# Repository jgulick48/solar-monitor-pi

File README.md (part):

# solar-monitor-pi

A Raspberry Pi image for monitoring a solar installation that uses EG4 / LuxPower inverters with the
WiFi datalogger dongle. Plug the Pi into the same network as the dongles and it finds them, starts
collecting data and serves dashboards. Nothing is sent to the internet, and the inverters are only
read, never changed.

## What's on it

| Part | What it does | Where |
|---|---|---|
| Setup page | Start page: dongles found, links, site setup form | `http://<pi>/` (port 80) |
| [lxp-bridge-go](https://github.com/jgulick48/lxp-bridge-go) | Reads every inverter's dongle (read-only mode) and publishes the values | internal |
| Mosquitto | MQTT broker between the bridge and Home Assistant | localhost only |
| VictoriaMetrics | Long-term history (5 years) of every inverter value | localhost only |
| Grafana | Dashboards, viewable without logging in | `http://<pi>:3000` |
| Home Assistant | Inverter entities (MQTT discovery), the Solar dashboard, alerts to phones | `http://<pi>:8123` |
| Advisor | Weekly analysis: batteries, panels, inverter or generator? | `http://<pi>/advisor` |
| Backups | Nightly backup to a USB stick, and restore | `http://<pi>/backup` |
| Battery health | Cell spread near full, temperatures, SOH, cycles, capacity check, BMS faults | `http://<pi>/battery` |
| Panels and inverters | A PV string or an inverter making far less than usual; the site far below the sunlight | `http://<pi>/panels` |
| Monthly report | Last month's solar, use, generator, battery and backups, against a year earlier | `http://<pi>/report` |
| Generator log | Every generator run, hours since the last service, service reminder | `http://<pi>/generator` |
| Wall display | Dashboard and up to two cameras on a screen plugged into the Pi's HDMI port | `http://<pi>/display` |
| go2rtc | Turns the cameras' RTSP(S) streams into video the display's browser can play | localhost only |
| cloudflared | Optional remote access to Home Assistant through your own Cloudflare account | `https://<name>.<your domain>` |
| cloudflared-support | Optional remote support: a helper's own Cloudflare Tunnel, while the owner allows it | the helper's hostnames |

## Hardware

- Raspberry Pi 4 (2 GB is enough, 4 GB recommended) and the official 5.1 V 3 A power supply.
- A **128 GB SSD** in a USB 3 enclosure with UASP (or a USB SSD such as a Samsung T7 / SanDisk Extreme).
  Five years of history for two inverters is a few GB; the extra space spreads the writes so the drive
  lasts. SATA-in-USB enclosures are safer than NVMe on a Pi 4 (its USB ports share about 1.2 A).
- Wired Ethernet on the same network (subnet) as the inverter dongles.
- Optional: a 1080p monitor or TV on the Pi's HDMI port (micro-HDMI 0, next to the power socket) for the
  wall display. Plugging it in, even later, starts the display.

## First boot

1. Flash the image to the SSD, plug it into the Pi's blue USB 3 port, connect Ethernet, power on.
2. Wait about five minutes, then open `http://solar-monitor.local/` (or the Pi's IP from the router).
3. The start page lists the dongles it found. Click **Finish setup** and enter the location, time zone,
   batteries, panels and generator. Saving applies it to Home Assistant and Grafana. The setup page lists its
   sections down the left side (a row of buttons under the header on a phone): the ones saved together with
   **Save site settings** have a green edge, the ones with their own button a blue edge. The list follows the
   page as it scrolls and marks sections with unsaved changes.
4. Open Home Assistant from the start page and create your account. The inverter entities are already
   there.

Give each dongle a fixed IP (DHCP reservation) in the router if you can. If a dongle's IP changes anyway,
the hourly scan finds it again by its serial number.

## Wall display

With a screen on the HDMI port the Pi shows a dashboard, laid out for 1920x1080:

- **Cameras** (left half, two stacked 960x540 tiles; without cameras the power figures use the whole screen).
- **Battery** (%, kWh stored, how long it lasts at the usual use), **solar**, **house load**, **battery power**
  (charging/discharging) and **generator**, with today's totals and the last 24 hours as a chart.
- **Notes**: dongles offline, inverter faults, low battery and, for a hand-started generator, from mid-afternoon on
  whether the battery lasts until the sun is back ("Start the generator before dark: ... about 4.2 kWh more is
  needed"), from the house's expected use and the solar forecast: a dull day tomorrow counts too
  ("tomorrow looks dull (about 6 kWh of solar expected) ...").
- **Any screen**: the screen mode comes from the TV's EDID: its own preferred mode, except that screens bigger than
  1920x1200 (4K TVs) run at 1920x1080, which the Pi handles much better with cameras and the TV scales up. The layout
  scales with the tighter of width and height, so 4:3, 16:10, 21:9 and 720p/768p screens fit, and a screen on its
  side gets the cameras on top and the figures below. The setup page shows the screen found and the mode used.
- **Clock**: 12-hour (4:41 PM) or 24-hour, set on the setup page (by default 12-hour with US units); the same format is
  used in the generator advice and the daily summary.
- **Sounds**: short chimes through the screen's speakers (HDMI) when a UniFi Protect camera sees something (a car horn for vehicles): doorbell
  ring and person by default, vehicle, animal and package optional, with a volume and *not during the screen-off
  hours*. *Play a test sound* on the setup page checks it. Repeats are limited: the same alert (same camera, same
  kind) at most once a minute by default, any two sounds at least 5 seconds apart, and the doorbell always rings
  (all adjustable); the camera still comes to the front of the screen. The kiosk points its sound at the HDMI port the screen is
  on (`~solar-display/.asoundrc`, Pi 4: HDMI-A-1 = vc4hdmi0); the screen or TV needs speakers.
- **Voice announcements** (optional, like UniFi's Alarm Manager; setup page: *Optional features* → *Voice
  announcements*): after the chime, or instead of it, Piper says what a camera saw, "Person at the Front door" /
  "Someone's at the Front door" (wording under *Cameras*, `{object}` and `{camera}`), in one of four English
  voices. Other features can use it for their own alerts (`modules.voice.announce(stack, text, chime=...)`; the display
  speaks announcements from the last two minutes, not during quiet hours). Piper runs in the optional `tts` service
  (`rhasspy/wyoming-piper`, the voice Home Assistant uses for local voice); it isn't in the image (about 200 MB):
  turning voice on downloads it and the voice once, then it works offline. Phrases are made ahead of time and cached
  (`state/tts-cache`). *Play a test announcement* on the setup page checks it.
- **Burn-in protection**: every 20 minutes the layout changes (cameras on the left or the right, or without cameras
  the tiles in order or reversed; the figures top-down or flipped, clock at the bottom), with a short fade, and every
  minute the whole page drifts a few pixels along a small circle, so no label, border or grid line stays on the same
  pixels for hours. `http://<pi>/display?layout=0` (to 3) shows one layout without rotating. The screen can also be
  switched off for set hours on the setup page.

### Solar forecast

`solar-collector` keeps Open-Meteo's irradiance forecast for each array (the same hourly request it already makes)
and turns it into expected output per hour for today and the next five days (`state/forecast.json`), scaled by the
advisor's calibration of this site's panels once it has one (0.8 of the model until then) and capped at the
inverters' solar input. It shows on the display's solar tile, as `sensor.site_solar_forecast_today` / `_tomorrow` in
Home Assistant, and drives the generator advice, which steps the battery through tonight and tomorrow in 15-minute
steps (forecast solar against the usual use) instead of assuming the sun takes over two hours after sunrise. With no
fresh forecast (no internet) the advice falls back to that rule.

It runs Chromium in kiosk mode inside `cage` (a one-app Wayland compositor; no desktop) as the locked
`solar-display` account (`solar-display.service`). It only starts when the display is turned on on the setup page,
the kiosk software is installed and a screen is connected; plugging a screen in starts it (udev rule). The browser's
profile lives in RAM. The same page is at `http://<pi>/display` from other computers, without the cameras.

**Camera checks.** The box re-fetches UniFi Protect's stream links at startup and every hour when Protect has changed
them (an old link can connect and send nothing), and checks each camera's video codec. The screen plays H.264 only: a
camera sending H.265 (Protect's *Enhanced Encoding*) shows a note in its place instead of a black box, and the setup
page says so; turn Enhanced Encoding off for that camera in Protect.

**Dongles that are gone** (a replaced dongle, a box moved to another site, test simulators) can be removed with
*Forget* on the start page: from the monitor, the bridge and Home Assistant.

**Camera load.** Playing the camera video is nearly all of the box's CPU work (test Pi 4: 41% of its four
cores with two medium-quality UniFi Protect streams, 27% with low, 5% with no video). The Protect section's *Camera
picture* is *Automatic* by default: low on a Pi 4, medium on a Pi 5 (boxes that update switch by themselves). The
video stops while the screen is off. go2rtc runs on the host network, listening on 127.0.0.1 only.

**Weather** shows in the same panel as the solar figures (setup page: *Optional features* → *Weather*, on by default;
how many forecast days and how fast they page are under *Weather on the screen*): now (temperature, conditions, feels-like, wind speed, gusts and direction, humidity, rain today), the next
days (high/low, rain chance, wind) and, where there's room, the next 12 hours. The forecast comes from Open-Meteo (free,
no key; every 30 minutes); a weather station set up on the setup page (Ecowitt, Tempest, WeatherLink, or pushing to
the box) supplies "now" with its own readings, wind included. In the US, National Weather Service alerts for the site
(every 10 minutes) appear with the other notes, red for severe ones. If the panel doesn't fit the screen (long notes, a
small screen), the hourly row is left out first.

**When the screen is on** (setup page, *Screen*): always; during **on-hours** (up to four lines such as
Mon-Fri 06:30-22:00 and Sat-Sun 08:00-01:00, past midnight allowed); **when someone's in the room**, from Home
Assistant occupancy, motion or presence sensors (`binary_sensor.*`, `person.*`, `input_boolean.*`; stays on for a set
time after the room empties); or during the on-hours *and* when someone's there. Camera events (doorbell, person, ...)
can turn it on for a few minutes outside those times. When it's off, the HDMI picture is switched off (`wlr-randr`;
most monitors and many TVs go to standby by themselves) and, if ticked, the **TV is put in standby and woken over
HDMI-CEC** (`cec-ctl`; SimpLink, Anynet+, Bravia Sync...), switched to the box's input when it wakes. The setup page
shows whether the TV answers CEC, and *Test: screen off for 15 seconds* tries it. Occupancy reaches the box through an
automation the box writes into Home Assistant (`packages/solar_display.yaml`); if Home Assistant goes quiet for 20
minutes the screen stays on. `solar-display-power.service` does the switching; CEC is sent only when the screen's state
changes, so a TV turned off with its remote stays off until the next change.

### Cameras (UniFi Protect)

Cameras are an optional feature (setup page: *Optional features* → *Cameras*; on for boxes that had cameras
before). Turning it off stops go2rtc and the Protect event listener and keeps the camera settings.

Up to 16 cameras; two are on screen at a time and they take turns every 15 seconds (only the two on screen are
played, so more cameras don't load the Pi).

**From UniFi Protect** (setup page, *UniFi Protect cameras*): enter the console's address and an API key (UniFi OS
-> Settings -> Control Plane -> Integrations -> Create API Key), tick the cameras for the screen and save. The box
fills in their stream links itself (Protect's Integration API; it creates a *medium* stream where there is none) and
keeps a connection to Protect's event stream: when a camera sees a **person, vehicle, animal or package** it comes to
the front of the screen with an amber frame and a label, and a **doorbell ring** with a red one, until a minute after
the event ends. Plain motion does the same only if *Also bring cameras to the front for plain motion* is ticked. The
key is kept in `state/protect.json` (mode 600); the console's self-signed certificate isn't checked.

**Phone notifications with the picture** (off until chosen): setup page, *Cameras*: tick *Doorbell* and/or *Person*.
When a UniFi Protect camera on the screen's list rings or sees a person, the box fetches the camera's picture from
the console and sends it through the notifications module: to its phones, with its quiet hours (a person waits
until morning; so does the doorbell, as a warning). The same camera and kind is sent at most every 5 minutes (a
choice from 1 minute to 1 hour). The picture shows in the Home Assistant app, at home and remotely. ntfy shows it as a
preview while remote access is on: the push carries a link to the picture on Home Assistant's public address. Pictures are kept for 2 days in `homeassistant/www/snap` under names that can't be guessed: Home
Assistant serves that folder without a login, which is what lets the app show them.

**By stream link** (any RTSP/RTSPS H.264 camera, no events): setup page, *Cameras*: name each camera and
paste its stream link. A camera added this way and later picked from UniFi Protect is dropped from the manual list
(same stream token or name), and the screen never shows the same camera in both places. In UniFi Protect: open the camera
-> Settings -> Advanced -> RTSPS, turn on **Medium** quality (720p: sharp enough for a 960x540 tile and light on
the Pi; the Pi 4 decodes H.264 in hardware) and copy the `rtsps://<console>:7441/<token>?enableSrtp` link.
`go2rtc` reads the streams (RTSPS without checking Protect's self-signed certificate) and serves them to the
display over MSE on 127.0.0.1 only, so the pictures aren't reachable from the network. The links are kept in
`state/display.json` and `go2rtc/go2rtc.yaml` (mode 600) and aren't shown again on the setup page (the token in
the link is effectively a password). Any camera with an RTSP/RTSPS H.264 stream works the same way.

For camera entities, motion and doorbell events in Home Assistant, add the **UniFi Protect** integration in
Home Assistant (Settings -> Devices & services; it's usually discovered automatically) with a local Protect user.

## Home Assistant: Solar dashboard and alerts

Home Assistant comes with a **Solar** dashboard in the sidebar and alerts, from `packages/solar_monitor.yaml`:

- **Site sensors** (`sensor.site_*`, `binary_sensor.site_*`): battery level, stored kWh and how long it lasts at the
  usual use, solar, house, battery and generator power, today's energy, dongles connected, fault code, alerts and the
  generator advice. They come from the box's `/api/ha`, the same totals and alerts as the wall display, added up over
  all inverters, so they don't depend on the inverters' own entity names.
- **Alerts**: battery low (5 min), inverter fault, dongle offline (10 min), no data (10 min) and, for a hand-started
  generator, *start the generator* (mid-afternoon, again 30 minutes before sunset if it hasn't been started; cleared
  when it runs). Each one shows in Home Assistant's notifications and on every phone signed in with the **Home
  Assistant app** (the alert is withdrawn from the phone once it clears). They can be switched off on the dashboard.
- **Daily summary** (setup page, *Daily summary*: on/off and time, default midnight): "24 kWh solar, 21 kWh used,
  battery down to 38%, generator 1.5 h (6.0 kWh). Today: about 13 kWh of solar expected." Sent before 06:00 it covers
  the day before, later the day so far; on Sundays it adds the week's totals and the advisor's latest finding.
- **Energy dashboard**: solar and battery are filled in on the first start; changes made in Home Assistant are kept.
  The generator isn't in it (Home Assistant has no off-grid generator source).

The package and the dashboard are replaced on every update (and Home Assistant restarted when they change), so edit
copies, not the originals: make your own dashboard in Settings -> Dashboards and your own automations.

## Check-up

`http://solar-monitor.local/check` (*Check-up* in the header) answers "is everything set up and working?" with one
line per item: green works, yellow works but deserves a look, red doesn't work, grey is optional and not set up.
Problems come first, each with what to do and a link to where it is fixed. The box checks the site details, the
inverter dongles, that data is being recorded, Home Assistant (running, and its owner account made), the solar
forecast, the panels and inverters, the box itself (temperature, power, disk, services) and the clock. Enabled modules add their own lines:
notifications (somewhere to send, and the last alert delivered), backup, remote access, cameras, freeze
protection and the boiler probe board. Open it after first setup, and whenever something seems off.

The **boiler probe board's** lines come straight from the board (its own web page at `boiler-probes.local`), not
through Home Assistant, so they work while it is being installed: whether it is on the network, what each probe port
reads, and what the two pump clamps and the heat call read. The box remembers which ports have had a probe. A port
that had one and has none now shows red by its number and name ("P3 (Boiler supply)"), which is what a pulled plug or
a loose wire looks like; a port that never had one is only listed as unused. After taking a probe out on purpose,
press *Forget missing probes* under *Boiler probe board* on the setup page.

## Away mode

For when nobody is at the property (setup page: *Optional features* → **Away mode**, then its switch on the start
page or under *Away mode* on the setup page, with an optional last day away). Nothing is switched: the alerts speak
earlier, and a report comes every day, so silence is never the only sign that all is well.

- **Freeze:** with freeze protection on, its "cold inside" level is raised (5 °F / 2.8 °C by default), and a hard
  freeze in the forecast is told even when the heat and the battery look fine.
- **Battery:** a warning when the battery has been within 15 points of the low-battery level for 10 minutes, while
  there is still time to come and start a generator.
- **Water:** with the water module watching the pump, any pump run is told, at most every 6 hours with the runs since
  the last word. Untick it if something uses water while you are away (an ice maker, a softener).
- **Daily report**, at 08:00 unless changed: the battery now, yesterday's lowest level, solar and generator hours,
  the watched temperatures, propane and the water pump. It is titled "All is well at <site>" when the check-up page
  has nothing red and no alert is open; otherwise "Away check: 2 things to look at", with those first.

It turns itself off the day after the last day away and says so. Home Assistant gets *Site away mode*. The margins
and the report time travel with a config export; being away does not.

## Following another site

A second box can show a site's inverters as if they were its own: a box at home showing the cabin, say. It must not
connect to the same dongles (two programs polling a WiFi dongle make it drop out), so the box at the site passes its
readings on instead.

- **At the site** (the source): Setup &rarr; *Optional features* &rarr; **Share this site**. The box's message broker
  gets a second listener on the network (port 8883, TLS with a certificate made on the box), and an account that
  can only read the inverters' raw frames. The bridge starts publishing every reply from the dongles as it came.
  The section shows a **share code**: the box's addresses, that account's password, the certificate and the dongles'
  ids. Send it privately. *Make a new code* changes the password, which cuts off every box using the old one.
- **On the other box** (the follower): *Optional features* &rarr; **Follow a site**, paste the code. It starts one
  *mirror* per dongle (the bridge image in mirror mode, up to 4), which reads the source's frames and answers this
  box's bridge like the dongle would. Home Assistant, the dashboards, the wall display and the advice then work
  unchanged. The mirror checks the source's certificate against the one in the code, only reads, and drops any
  write: a follower can never change the inverter.
- **Reaching each other:** the follower must reach the source's address on port 8883: the same network, or a VPN
  between the sites (enter the VPN address in *The other box's address*). Through the source's remote-access tunnel
  is not supported yet.
- **When the source stops getting data** its frames go stale after 2 minutes and the follower shows the inverter
  offline too. The *Check-up* page says whether each mirror is getting data.
- **A box with inverters of its own** that also follows a site adds the two together as one system; following is
  meant for a box without its own. On the same network, the follower stops reading a followed dongle directly and
  the hourly scan leaves it alone.

## History: this year against last

`http://solar-monitor.local/history` (*History* in the header) shows each of the last 12 months against the same
month a year earlier, with the change in percent: solar, use, the highest load, the lowest battery level, generator hours, and propane and water while those
modules are on. The weather is beside them, since a colder or windier month explains more propane or generator
time: the average outdoor temperature ("5 °F colder"), heating degree days, the average wind and the strongest gust. The month under way is compared with the same days last year, not the whole month. Only days with
data are counted, and a month that misses days says how many it has. Until the box has a year of data the earlier
column is empty.

The figures come from per-day totals the collector stores once each day is over (`site_day_solar_kwh`,
`site_day_used_kwh`, `site_day_generator_hours`, `site_day_generator_kwh`, `site_day_low_soc`,
`propane_day_used_gal`, and the weather: `site_day_temp_high_c`, `site_day_temp_low_c`, `site_day_temp_avg_c`,
`site_day_hdd`, `site_day_wind_avg_ms`, `site_day_gust_max_ms`), with days cut at the site's midnight. The weather
is the station's when the day has enough of its readings, else Open-Meteo's. On its first runs it goes back to the oldest inverter
data the box has, 90 days an hour. Grafana has the dashboard *History: this year against last*: 30-day totals and
daily bars against the same days a year earlier. The data is kept for 5 years.

### Monthly report

On the 1st of each month, after 8:00, the box sends one notification about the month that just ended:
*Solar report for October 2026*. It has the solar made, the power used, the highest load, the lowest battery level,
generator hours with fuel and cost, and propane and water while those modules are on. Solar, use, propane and water
are compared with the same month a year earlier once the box has one. It ends with battery health and the last
backup as they stand that day. It is an "info" notification, so it follows the same routing and quiet hours as the
daily summary.

`http://solar-monitor.local/report` (*Report* in the header) shows the same report as a table, and the 11 months
before it. The month figures are the History page's, so the two always agree. A box installed or updated after the
7th makes last month's report for the page but doesn't send it late. The setup page's *Daily summary and monthly
report* section turns the notification off; the page stays.

**Hourly weather, for heat-loss work.** Beside the outdoor temperature and the sunlight, the box now records the
wind: a weather station's as it reads it (`site_wind_speed_ms`, `site_wind_gust_ms`; average them over an hour), and
Open-Meteo's for every hour (`site_openmeteo_wind_ms`, `site_openmeteo_gust_ms`, at 10 m), together with Open-Meteo's
sunlight on level ground (`site_openmeteo_ghi_wm2`, the hour's mean). With the heat the boiler module measures,
that is what a building's wind-driven heat loss and its solar gain can be told apart from. On the first fetch after
this update the box brings in the last 92 days of Open-Meteo's wind and sunlight.

## Settings file (export and import)

*Setup* &rarr; *Settings file* (`/config`) downloads this box's settings as one JSON file and imports such a file from
another box, for a replacement box or a second site set up the same way.

- **In the file:** the site details, the wall display, the weather source, updates, the UniFi Protect address and
  camera choice, and the settings of the generator, notifications, cameras, voice, weather, propane, water, boiler,
  freeze protection and probe board modules (and whether each is on).
- **Not in it:** history (that is what backups are for), and what belongs to one box: remote access, remote
  support, SSH keys, the backup stick, the Zigbee and Z-Wave radios and the box's own passwords.
- **Secrets** (API keys, tokens, the cameras' stream links, the ntfy topic) are left out. The web page never exports
  them, since anyone on the network can open it. To include them, encrypted with a passphrase of 8 characters or
  more (AES-256, PBKDF2), export on the box itself:
  `sudo python3 /opt/solar-monitor/src/setup/configfile.py export --secrets > solar-config.json`
- **Import** shows first what would change, setting by setting (secrets as "(hidden)"), and saves nothing until
  *Import these settings* is pressed. Give the passphrase to bring the secrets too; without it the box keeps its
  own. Values of the wrong kind and anything this version doesn't know are skipped and listed. The settings as they
  were are kept in `state/config-before-import.json`.

## The box's own health and a test notification

The start page's **This box** card (and Home Assistant's *Site box health*, *temperature*, *disk free* and *SSD wear*
sensors, with a *monitor box needs attention* alert) watches the Pi itself:

| Check | Worth a look | Needs attention |
|---|---|---|
| CPU temperature | 70 °C | 80 °C |
| Power supply (`vcgencmd get_throttled`) | under-voltage or throttling since the last start | now |
| SSD free space | under 15% | under 5% or 2 GB |
| SSD health (`smartctl`, through the USB adapter when it allows) | 70% of rated life used | 90%, media errors, failed self-assessment |
| Containers | | any not running |
| Dongle drop-outs (24 h) | 6 or more | |

**Send a test notification** (start page, Home Assistant card) checks that alerts reach the phones: it lists the phones
with the Home Assistant app signed in to the box and triggers the same notification script the alerts use, through a
local-only webhook whose id is a per-box secret.

## Backups (USB stick)

Plug a USB stick into the Pi (FAT32, exFAT, ext4 or NTFS, as most sticks come; 16 GB or more) and choose it on the
**Backups** page (`http://<pi>/backup`). The box never formats it. Every night at about 01:30 it backs up the settings
and passwords (`state/`), Home Assistant (config, accounts, dashboards, and its database as a consistent copy), the camera
config and, unless turned off, the whole inverter history (a VictoriaMetrics snapshot). The backups are
[restic](https://restic.net) snapshots in a `solar-monitor-backup` folder (deduplicated, so each night only adds what
changed); 7 daily, 4 weekly and 6 monthly are kept. The stick is mounted only while a backup runs, so it can be pulled
out at any other time.

**The key to the backups is on the stick, next to them**, so a box whose SSD died can be restored from the stick alone.
That means whoever has the stick can read the box's passwords and camera links: keep it in the Pi.

To restore (for example onto a new SSD): flash the image, start the box, open the Backups page, choose the stick and
**Restore from the stick**. It stops everything, puts back the newest backup, rebuilds the generated config and starts
again (a few minutes). Home Assistant alerts (and the start page shows it) when there has been no good backup for two
days.

restic runs in a container (`backup` service in `stack/compose.yaml`, profile `backup`), so boxes updated from older
versions download it on the first backup.

## Battery health

The **Battery health** page (`http://<pi>/battery`) looks at the whole battery bank as the inverters hear it from the BMS
(with several inverters, the highest and lowest cells of any of them):

| Check | Good | Worth a look | Needs attention |
|---|---|---|---|
| Cell spread at 98% or more (per day, last 14 days) | under 50 mV | 50-100 mV | over 100 mV |
| Days since a full charge (bounded by the history) | under 14 | 14-30 | over 30 |
| Cell temperature (now and 24 h) | | | 0 °C or below, 45 °C or above |
| State of health (BMS) | | | under 80% |
| BMS fault / warning code (now and 24 h) | 0 | warning | fault |
| Capacity estimate vs the size on the setup page | | under 80% or over 125% | |

LiFePO4 cells sit near 3.3 V for most of the charge, so imbalance only shows near full, which is also where the BMS
balances them. The capacity estimate is the energy taken out per 1% of charge on discharges of 30% or more, times 100: it
follows the BMS's own charge counter, so it checks the BMS and the setup page's battery size rather than the cells
themselves. Home Assistant gets the figures as sensors (*Site battery health*, *cell spread when full*, *state of health*,
*cycles*, *cell temperature low/high*, *capacity estimate*), a *Battery needs attention* alert, and a Battery health
section on the Solar dashboard. A BMS fault also shows on the wall display.

Grafana has the dashboard *Battery and generator*: the cell spread near full, the highest and lowest cell, cell
temperatures, state of health, cycles and the capacity estimate over time (a slow fall over the years is the
batteries ageing), and below them the generator: its power, hours and energy per day, and the hours since its
service. It uses the same queries as this page and the generator log.

## Panels and inverters

Some faults look normal at a glance: with two inverters one can stop while the other carries everything, and a
tripped string breaker only shows as "a bit less solar". The **Panels** page (`http://<pi>/panels`) checks every
5 minutes:

| Check | Reported when |
|---|---|
| Each PV string | It makes under 20% of what its usual share of the site's solar would give now (and that is 300 W or more), over the last 2 hours. All of one inverter's strings out is reported as that inverter. |
| Each inverter's output | It supplies under 10% of its usual share of the house (500 W or more) for 30 minutes while the others carry it. |
| The whole site | Under 40% of what the sunlight should give over the last 2 full hours: snow, dirt, a tripped main PV breaker. |

There is nothing to set up. A string's usual share is learned from the same 2 hours of the day over the last 4 weeks
(strings facing different ways have shares that change through the day), and needs 5 comparable days first. Nothing
is judged in poor light or while the battery is at 95% or more: the inverters then hold the panels back, and not
evenly. On a site whose battery is full by late morning every day, that leaves the morning for these checks.

The whole-site check needs to know what the sunlight should give. With a weather station that has a solar sensor
that is measured, and a low reading is an alert after 2 hours. Without one it comes from the weather forecast, which
can miss cloud: it is then only noted on the page, and becomes an alert when the last day of sunlight was as low. It
starts once the advisor has tuned the forecast to the site (a few weeks of data).

A finding stays until the same check passes again, so it doesn't clear at dusk and come back at dawn. Home Assistant
gets *Site solar check* (ok, note, warn), a *Site solar needs attention* problem sensor and one alert through the
usual notifications; it is also a line on the check-up page and a card on the start page. A dongle that is offline or
silent has its own alerts already.

## Overload warning

Each inverter has its own limit, and each of its two 120 V legs has half of it (a 6000XP: 6 kW, 3 kW a leg). So two
inverters with 12 kW between them can trip at 3 kW on one leg while the total looks comfortable. The box watches every
inverter's whole output and each leg, in VA where the inverter reports it (the limit is in VA, and a motor draws
more VA than W), and takes the tightest one as a percentage of its limit:

- **90% or more** (the highest 1-minute average in the last 3 minutes): an alert at once, naming the inverter and
  leg: turn something off before starting another big load. It clears after 10 quiet minutes.
- **80% or more at some point today**: noted on the start page, no alert.

Home Assistant gets *Site inverter load* (%), *Site peak load today* (kW) and *Site inverters near limit*. The day's
highest load is also kept in the history (the History page and the Grafana History dashboard), filled in for
earlier days too. The limit is the model's continuous rating from the setup page; readings come about every 10
seconds, so a shorter surge isn't seen.

## Generator log and service reminder

The generator is an optional feature (setup page: *Optional features* → *Generator*; on unless the site had chosen "No
generator"). Its section says how it is started (by hand or auto-start from the dry contact), its size and fuel; the
start-the-generator advice on the wall display is for a generator started by hand. Turning it off is what "No generator"
was: no generator tile or advice, no log or reminders.

**When to stop it.** While a hand-started generator runs, the box repeats the same overnight calculation from the
battery's level now, at any time of day: "Keep the generator running about 40 min more: about 2.7 kWh more is needed
to last until the sun is back", using the charge rate measured over the last 10 minutes (or the Chargeverter's amps).
When the battery will last with a margin (the larger of 0.5 kWh and 5% of the battery): "The generator can be shut
down." That is said once per run by the wall display's voice and sent as a notification; Home Assistant has
*Site generator can stop*. It only advises: an auto-start generator follows the inverter's own stop setting.

**Following a run.** For a generator somebody has to walk out to, the box follows each run as it happens (both
switches are in the generator's section of the setup page, on by default):

- **Started and stopped.** A notice when the generator has run for 3 minutes ("Running since 17:42, giving about
  4.8 kW. Battery 41%. It needs to run about 2 h 30 min...") and when it has been off for 5: how long it ran, the
  energy, the fuel and cost, the battery before and after, and the fuel on hand. If it stopped while the box was
  still saying "keep it running" (somebody shut it down early, or it ran out of fuel), the notice is a warning and
  says how many kWh are still needed.
- **Reminders that follow the battery.** Home Assistant says "start the generator" once, again before sunset and
  every 4 hours. For a generator started by hand the box adds a reminder each time the battery has fallen 10 more
  points while it still isn't running, and one "Start the generator now" when the battery is within 2 hours of the
  low-battery level, never within 30 minutes of the last word. They are critical alerts, so they come through in
  quiet hours.
- **Fuel on hand.** On the Generator page, enter the gallons in the cans or the tank after filling up. The box
  takes off what each run uses (the log's own fuel figures: your measured gallons per hour, else the typical figure
  for the generator's size at the load it carried) and shows the gallons and the hours of running left there, on
  the start page and in Home Assistant (*Site generator fuel on hand*). It warns once when fewer hours are left
  than you set (2 by default), and a reminder says so when the fuel on hand is less than the run that is needed.
  It is a count, not a gauge: correct it whenever you check the tank.

**Solar to spare.** Once the battery is full, solar the house doesn't use is thrown away. With the battery at 90% or
reaching it within the hour, and the panels able to make at least 1 kW more than the expected use for an hour or
more, the wall display says "About 2 kW of solar to spare until 3:00 PM: a good time to run big loads" (the figure
is what can be counted on for the next hour). Home Assistant has *Site spare power* (W, 0 when there is none), which
an automation of your own can use to start a water heater or a charger; the box switches nothing. A phone
notification, at most once a day, is a checkbox under *Batteries* on the setup page, off by default.

**The next 5 days.** The solar forecast reaches 5 days ahead. The box sets each day's forecast against its expected
use and follows the battery through them, hour by hour, from its level now. A day is dull when the panels will make
less than the house uses. With at least 2 dull days and a battery that would reach the alert level, the wall display
and Home Assistant (*Site outlook*: ok, dull or storm) say what it will take: "3 dull days ahead (Thursday to
Saturday): expect about 9 h 30 min of generator (49 kWh); propane is at 34%". The hours need the charger's amps;
the tank is named for a propane generator with the propane module on. Without a generator it says when the battery
gets low. A storm warning from the weather module (National Weather Service, US) adds a short checklist. A
notification is sent when the outlook first turns, at most once in 20 hours. The sensor's `outlook_days` attribute
has each day's solar and use.

**Freeze protection (a module, off by default).** Pick up to 4 temperatures from Home Assistant on the setup page:
a slab or pipe probe, a room sensor, a thermostat. A critical alert is sent when one stays below the threshold
(40 °F / 4.4 °C by default) for 5 minutes, and cleared once it is 1 °C above it again. With the weather module on, a
warning comes hours earlier: when a hard freeze (20 °F / -6.7 °C by default) is forecast in the next 24 hours while
the boiler module reports a fault or the battery is at its low level. A watched sensor that stops reporting for 30
minutes raises its own alert. The wall display gets a panel, Home Assistant gets *Site freeze alert*, *Site lowest
watched temperature* and *Site forecast low*, and the Home dashboard a section. It needs no boiler module and
switches nothing.

**Expected use.** The advice, "lasts about" and the day's battery high need to know how much the house will use, and
when. The box learns it per hour of the week from the last 8 weeks (the median, so one-off days don't count), scaled
by how the last 3 days compare with usual. It checks itself: every hour it replays the last 28 nights (4 PM to
9 AM) both ways, and uses the weekly profile only where it predicted better than the plain average of the last 3
days; otherwise, and until there are 2 weeks of history, it stays with that average. The collector's log says which
is in use and why; Home Assistant gets *Site expected use tomorrow* (kWh), with the method as an attribute.

With a **Chargeverter** (or another DC charger), enter the current it's set to (for example 40 A). The advice then also
says how long to run the generator: "About 4.2 kWh more is needed. Run it about 2 h with the charger at 40 A (2.1 kW)."
That's the kWh needed divided by the charger's power, its amps times the battery's voltage, rounded up to 15 minutes.
The voltage is the battery's resting voltage, or 51.2 V when the inverters don't report it, so the estimate errs on the
long side. With the generator's size entered too, it warns when the charger is set to draw more than the generator
can give. Home Assistant gets the run time as the `advice_run_hours` attribute of *Site generator advice*.

The box finds every generator run in the inverter history, a minute at a time, two ways:

- **On the inverters' GEN input** (usually auto-started by the dry contact): generator input power above 200 W.
  Service every **200 hours**.
- **Through a DC charger** such as a Chargeverter: the battery BMS's charging power more than 500 W above what the
  inverters put into the battery. Service every **100 hours**.

Dips under 5 minutes don't end a run; runs under 3 minutes (10 for the charger estimate) are ignored. The first time,
it works through the existing history (up to 400 days). The **Generator** page (`http://<pi>/generator`) lists the runs
(start, hours, energy, peak) and the hours since the last service, with a **Serviced** button (enter the hours it has
already run if the oil was changed earlier). Home Assistant gets *Site generator hours since service*, *last run*,
*running* and *service due* sensors and sends a reminder when a service is due. The generator power everywhere (wall
display, Home Assistant, daily summary) now includes a generator charging through a DC charger.

**Fuel and cost.** Each run on the Generator page also shows the fuel it used and what that cost, with totals by
month and for the last 30 days. The fuel comes from your own *measured fuel use* (gallons per hour, on the setup
page under Generator) when you enter it; otherwise it is an estimate: the typical use of a generator of that size
and fuel at the load the run actually carried. The cost uses the fuel price under Costs. Nothing is stored: correct
the size or the price and the whole log is repriced. Home Assistant gets *Site generator fuel 30 days* (with the
cost as an attribute). Figures are in gallons, as the fuel price is.

State: `state/generator.json`; `setup/genlog.py` (run by the collector every 5 minutes; `genlog.py update` by hand).

## Remote access (Cloudflare Tunnel, optional)

To reach Home Assistant (and the Home Assistant phone app) away from home without opening anything on the router, fill in
**Remote access** at the bottom of the setup page (`http://<pi>/setup#remote`):

- **Cloudflare account ID**: on the Cloudflare dashboard, a domain's overview page, right-hand column.
- **Name** and **Domain**: Home Assistant will be at `https://<name>.<domain>`, e.g. `solar.example.com`. The domain must
  already be on that Cloudflare account.
- **API token**: Cloudflare &rarr; My Profile &rarr; API Tokens &rarr; Create Custom Token with *Account &middot; Cloudflare
  Tunnel &middot; Edit*, *Zone &middot; DNS &middot; Edit* and *Zone &middot; Zone &middot; Read*, limited to that account and domain.

The box then creates a remotely managed tunnel, points it at Home Assistant only (`http://localhost:8123`; any other
hostname gets a 404), adds a proxied CNAME `<name>.<domain>` &rarr; `<tunnel id>.cfargotunnel.com` and starts the
`cloudflared` container (compose profile `tunnel`, switched on by `COMPOSE_PROFILES=tunnel` in the generated `.env`).
Home Assistant's `external_url` is set to the new address, so the phone app uses it away from home, and it trusts the
forwarded client address from localhost only (`use_x_forwarded_for` and `trusted_proxies` in `.storage/http`, edited while
Home Assistant is stopped: since 2026.11 Home Assistant ignores `http:` in YAML).

- Only Home Assistant is published. The setup page, Grafana and the cameras stay on the local network.
- It refuses to turn on before the Home Assistant owner account exists, since anyone who found the address could
  otherwise claim it. Turn on two-factor authentication in your Home Assistant profile.
- It never overwrites a DNS record it didn't make; pick another name if `<name>.<domain>` is taken.
- **Turn remote access off** stops `cloudflared` and, unless unticked, deletes the tunnel and its DNS record at Cloudflare.
- The API token and the tunnel's run token are kept in `state/modules/tunnel.json` and `state/tunnel.env` (mode 600) and are
  included in the USB backups.

## Remote support (optional)

For troubleshooting a box from elsewhere. The **helper** sets up the access in their own Cloudflare account; the **owner**
turns it on (and off) on the box's setup page (`http://<pi>/setup#support`). It is off by default.

Helper, the quick way (`tools/support-helper.py`, plain Python, from a clone of this repo):

1. Once: create a Cloudflare API token (My Profile &rarr; API Tokens &rarr; Custom token) with *Account: Cloudflare Tunnel
   Edit*, *Account: Access: Apps and Policies Edit*, *Account: Access: Service Tokens Edit*, *Zone: DNS Edit* and
   *Zone: Zone Read* for your domain; save it in `~/.cache/cf-solar-support-api` (mode 600). Then
   `tools/support-helper.py init --account <account id> --domain example.com --email you@example.com --key ~/.ssh/id_ed25519.pub`.
2. Per box: `tools/support-helper.py new neighbor` makes the tunnel, the hostnames `neighbor-ssh`, `neighbor-setup`,
   `neighbor-grafana` and `neighbor-ha` on your domain, their DNS records and a Cloudflare Access app (your emails, plus
   a service token for scripts), and prints a **support code**. Send it to the owner privately.
3. The owner pastes the code on the setup page (Remote support) and presses *Turn remote support on*.
4. `tools/support-helper.py ssh neighbor` logs you in (needs `cloudflared`); the setup page is at
   `https://neighbor-setup.example.com`. `list` shows your boxes and whether they're connected; `remove neighbor` deletes it all.
5. Optional: `tools/support-helper.py ha neighbor open` takes `neighbor-ha` out of the Access app, so only Home
   Assistant's own login page stands in front of it and its phone app can connect to that address. It is refused
   until Home Assistant has its owner account (otherwise the first visitor could create it). Home Assistant's login
   is then reachable from the internet: use a strong password and turn on two-step login for its accounts.
   `ha neighbor protected` puts the Cloudflare login back. The setup page, Grafana and SSH always stay behind it.

Helper, by hand in the Cloudflare dashboard:

1. Cloudflare Zero Trust &rarr; Networks &rarr; Tunnels &rarr; **Create a tunnel** (cloudflared), name it after the site.
   Copy the token (the long string after `cloudflared service install`).
2. Add public hostnames for what you need, all on the box itself:
   `ssh://localhost:22` (SSH), `http://localhost:80` (setup page), `http://localhost:3000` (Grafana),
   `http://localhost:8123` (Home Assistant).
3. Protect those hostnames with a Cloudflare Access application (your identity provider; optionally a service token
   for scripts). Without it, anyone who learns the setup page's hostname can use it.
4. Give the owner the token and your SSH public key.

Owner: paste the token and key under **Remote support**, choose when it switches off (1, 3, 7, 14 or 30 days, or only by
hand) and press **Turn remote support on**. The start page shows a "Remote support is on" banner with an off button the
whole time. While it is on the box:

- runs `cloudflared-support` (compose profile `support`) with the helper's token;
- adds the helper's key to the `solar` account (a marked block in `~solar/.ssh/authorized_keys`, other keys untouched)
  and allows `sudo` without a password (`/etc/sudoers.d/solar-support`): **full administrator access**;
- starts SSH if it wasn't running, listening on localhost only (so only the tunnel reaches it) and for keys only
  (`/etc/ssh/sshd_config.d/solar-support.conf`). If the owner had turned SSH on themselves, it is left as it is.

Turning it off, by hand or when its time is up (the collector checks every minute, and re-applies it after a reboot while
it is on), removes all of that again. Settings: `state/modules/support.json` and `state/support.env` (mode 600).

Connecting (helper): `ssh -o ProxyCommand="cloudflared access ssh --hostname %h" solar@<ssh hostname>`; add
`--service-token-id <id> --service-token-secret <secret>` to the `cloudflared` command for a non-interactive login.

## Advisor

The start page's **Advisor** answers "what would help this system most?" from the site's own history. It
runs every week (Sunday night) or on demand:

1. **Solar that could have been made**: sunlight on each array's tilt and direction, from a local weather
   station or Open-Meteo, calibrated against the inverters' actual output while the batteries weren't
   full. That shows the solar lost because the batteries were full, which the inverters' own readings hide.
2. **What happened**: load, solar, lost solar, low battery days and generator charging by month, plus
   charging the inverters didn't do themselves (a Chargeverter or other DC charger shows up as the
   battery's BMS current being higher than the inverters' battery power). The generator's energy and runs per
   month are the generator log's, so they agree with the Generator page and the monthly report; while the log is
   off or still working through the history, they are counted from the 15-minute history instead, and the page
   says so.
3. **Options compared**: the period is replayed with +1/+2/+4 batteries, +25/50/100% panels (capped at
   the inverters' solar input, with an extra inverter where that limits it) and an automatic generator.
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
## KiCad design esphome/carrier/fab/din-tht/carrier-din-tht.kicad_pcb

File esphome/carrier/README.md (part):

# Carrier board for the boiler probes

A 100 × 60 mm two-layer PCB that the Waveshare ESP32-P4-ETH (with its PoE module) plugs into. It gives the board
eight probe ports and the boiler module's other inputs, and fits the enclosure in `../enclosure/`.

| THT (hand-soldered) | SMD (factory-assembled resistors and capacitors) |
| --- | --- |
|  |  |

## What's on it

| Part | Where | Connects to |
| --- | --- | --- |
| 2 × 1×20 female headers (J1, J2) | middle | The ESP32-P4-ETH's header pins; its RJ45 end overhangs the board's left edge by 1.9 mm so the jack ends flush with the enclosure |
| 8 probe ports P1–P8 (J3–J10) | P1–P4 along the front (RESET side), P5–P8 along the back | One 1-Wire bus per port: P1 GPIO33, P2 GPIO27, P3 GPIO23, P4 GPIO21, P5 GPIO32, P6 GPIO26, P7 GPIO22, P8 GPIO20, each with its own 4.7 kΩ pull-up. Pins G (GND), D (data), V (3.3 V) |
| HEAT (J11) | right edge, front | The thermostat's 24 VAC call for heat on the outer two pins (middle empty), isolated by a PC814 / EL814 AC-input optocoupler through 10 kΩ. GPIO46 reads low while the call is on (10 kΩ pull-up, 1 µF to smooth the 120 Hz ripple) |
| CT1, CT2 (J12, J16) | right edge, back and middle | Two 3.5 mm stereo jacks (CUI SJ1-3523N) for SCT-013 1 V current clamps, plugged straight in. The SCT-013's plug uses tip and sleeve only: sleeve to GPIO16 (CT1) or GPIO17 (CT2), tip to BIAS (half of 3.3 V from 2 × 10 kΩ and 10 µF), ring not connected (OpenEnergyMonitor's wiring) |
| OLED (J13) | back left | GND, VCC (3.3 V), SCL (GPIO8), SDA (GPIO7): the pin order of the common 0.96" SSD1306 modules. The ESP board already has I²C pull-ups |
| BTN (J14) | front left | GPIO47 and GND, for a push button on the lid (use the internal pull-up) |
| SPARE (J15) | front left | 3V3, GND, GPIO48, GPIO19, GPIO18, GPIO15 |
| 4 × M3 holes | corners | The enclosure's standoffs |

RESET and BOOT on the ESP board stay reachable through the enclosure's side holes: nothing tall sits in line with
them (x = 16.1 mm).

The probe ports and the HEAT input use 3-pin 5.08 mm **pluggable** terminal blocks (right-angle header on the
board, screw plug on the cable), such as uxcell's "3-Pin 5.08mm Pitch Right Angle PCB Screw Terminal Block" sets:
nine of a pack of ten cover them. The footprint is KiCad's Phoenix MSTBA (same pin layout); check that the headers' pins
fit its 1.4 mm holes before ordering.

## Through-hole parts (THT version)

Soldered to the board (checked against `fab/tht/carrier-tht.kicad_pcb`):

| Ref | Qty | Part | Notes |
| --- | --- | --- | --- |
| J1, J2 | 2 | 1×20 female pin header, 2.54 mm, 8.5 mm tall | Sockets for the ESP32-P4-ETH |
| J3–J10 | 8 | 3-pin 5.08 mm pluggable terminal block (right-angle header + screw plug) | Probe ports P1–P8 |
| J11 | 1 | 3-pin 5.08 mm pluggable terminal block, as above | HEAT (24 VAC on the outer pins) |
| J12, J16 | 2 | 3.5 mm stereo jack, CUI SJ1-3523N (through-hole, right-angle) | Pump clamps CT1, CT2. Use this part or a pin-compatible one: the holes are made for it |
| J13 | 1 | 1×4 male pin header, 2.54 mm | OLED lead |
| J14 | 1 | 1×2 male pin header, 2.54 mm | WAKE button lead |
| J15 | 1 | 2×3 male pin header, 2.54 mm | Spare GPIOs (optional): 3V3, GPIO48, GPIO18 on the row with the square pad; GND, GPIO19, GPIO15 on the other |
| R1–R8 | 8 | 4.7 kΩ, ¼ W, axial (6.3 mm body) | Probe pull-ups; holes 10.16 mm (0.4") apart |
| R9 | 1 | 10 kΩ, ¼ W, axial | Heat-call input (24 VAC side) |
| R10 | 1 | 10 kΩ, ¼ W, axial | Heat-call pull-up (GPIO46) |
| R11, R12 | 2 | 10 kΩ, ¼ W, axial | Clamp bias divider |
| U1 | 1 | PC814 optocoupler, DIP-4 (AC input) | EL814 works too; a DIP-4 socket is optional |
| C1 | 1 | 1 µF ceramic, 5 mm lead spacing, ≥ 16 V | Heat-call smoothing |
| C2 | 1 | 10 µF ceramic, 5 mm lead spacing, ≥ 10 V | Clamp bias. A radial MLCC fits the holes; a small electrolytic needs its legs bent to 5 mm, + toward BIAS |
| C3 | 1 | 100 nF ceramic, 5 mm lead spacing | 3.3 V decoupling |

In short: 2 female 1×20 headers, 9 pluggable 3-pin blocks, 2 jacks, 8 × 4.7 kΩ, 4 × 10 kΩ, 1 PC814, 3 capacitors
(1 µF, 10 µF, 100 nF) and 3 small male headers. If the ESP32-P4-ETH came without headers: 2 × 1×20 male headers,
soldered with the pins pointing down into the sockets.

To go with it (enclosure and wiring):

| Qty | Part | For |
| --- | --- | --- |
| 1 | Waveshare ESP32-P4-ETH with its PoE module (B) | The board itself |
| 1 | 0.96" SSD1306 I²C OLED module, 4 pins (GND VCC SCL SDA) | Display behind the top's window |
| 1 | 4-wire female-female Dupont lead, about 15 cm | OLED to J13 |
| 1 | 12 mm panel-mount momentary push button, normally open | WAKE, in the top |
| 1 | 2-wire lead with a 2-pin female Dupont housing | WAKE button to J14 |
| 4 | M3 × 6 self-tapping screws | Carrier onto the enclosure's standoffs |
| 4 | M3 × 12 self-tapping screws | Joining base and cover |
| 4 | M2 × 4 self-tapping screws | OLED onto its posts |
| 2 | 4 mm (#8) screws | The enclosure's mounting tabs |
| 3–8 | DS18B20 waterproof probes, silicone cable | One per port (G, D, V) |
| 0–2 | SCT-013 current clamps, 1 V output | CT1, CT2: plug straight in |

## DIN-rail version

The same circuit on a 111.5 × 88 mm board for the DIN-rail case (`../enclosure/boiler-probes-din.scad`). It uses
the same pins as the board above, so the firmware (`../boiler-probes.yaml`) and the parts list are the same.

| THT | SMD |
| --- | --- |
|  |  |

On the rail, everything plugs in from above or below and nothing from the sides, so other modules can sit against it:

| Where | What |
| --- | --- |
| Top edge | CT1 and CT2 (left), then P1–P4. The ESP board's USB-C jack is above CT2, reached through the case's top |
| Bottom edge | The ESP board's RJ45 jack (left), then P5–P8 and HEAT |
| Left | The ESP32-P4-ETH on end: RJ45 down, USB-C up, its BOOT side and the PoE module's overhang toward the left edge |
| Middle | OLED, BTN and SPARE headers, in the open, where their leads have the case's full height |
| Four notches in the edge | Top (between CT2 and P1), two on the right, bottom left: the case's pillars stand in them |
| 5 × M3 holes | The case's standoffs |

What differs from the box board:

- **RESET** is on the ESP board's inner edge and can't be reached from outside the case; BOOT can, through the left
  wall. To flash over USB, hold BOOT while plugging the network (PoE) cable in, or take the cover off.
- **The clamp jacks sit under the ESP board's USB end** (they are 5 mm high, the ESP board is 11 mm up).
- **HEAT** is an ordinary bottom-edge port (24 VAC on its outer two pins, as before).

Not built or tested. The routed boards' DRC lists only ground pads that join the pour through fewer thermal spokes
than KiCad likes; nothing is unconnected.

## Files

| File | What |
| --- | --- |
| `build_board.py` | Builds the board in KiCad 9's Python: parts, placement, nets, labels; then imports the routes and adds the ground pours |
| `build.sh` | The whole build in Docker: place, route with [Freerouting](https://github.com/freerouting/freerouting) 2.1.0, ground pours, DRC, Gerbers, drill files, renders, and for SMD the JLCPCB files. Variants: `tht`, `smd`, `din-tht`, `din-smd` (all four by default) |
| `jlc_files.py` | JLCPCB's BOM and placement (CPL) files for the SMD version |
| `fab/<variant>/carrier-*.kicad_pcb` | The routed board, to open in KiCad |
| `fab/<variant>/carrier-*-gerbers.zip` | **Upload this to the PCB maker**: Gerbers and drill files |
| `fab/smd/` and `fab/din-smd/`: `carrier-*-jlc-bom.csv`, `-cpl.csv` | For JLCPCB's assembly service (top side) |
| `fab/<variant>/drc.rpt` | KiCad's design rule check |

## Status

- **Both boards route completely** (0 unconnected pads; `build.sh` re-routes until KiCad agrees). The DRC's remaining items are silkscreen ones (outlines
  running past the board edge where the pluggable headers overhang it on purpose, labels touching outlines) and, on
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
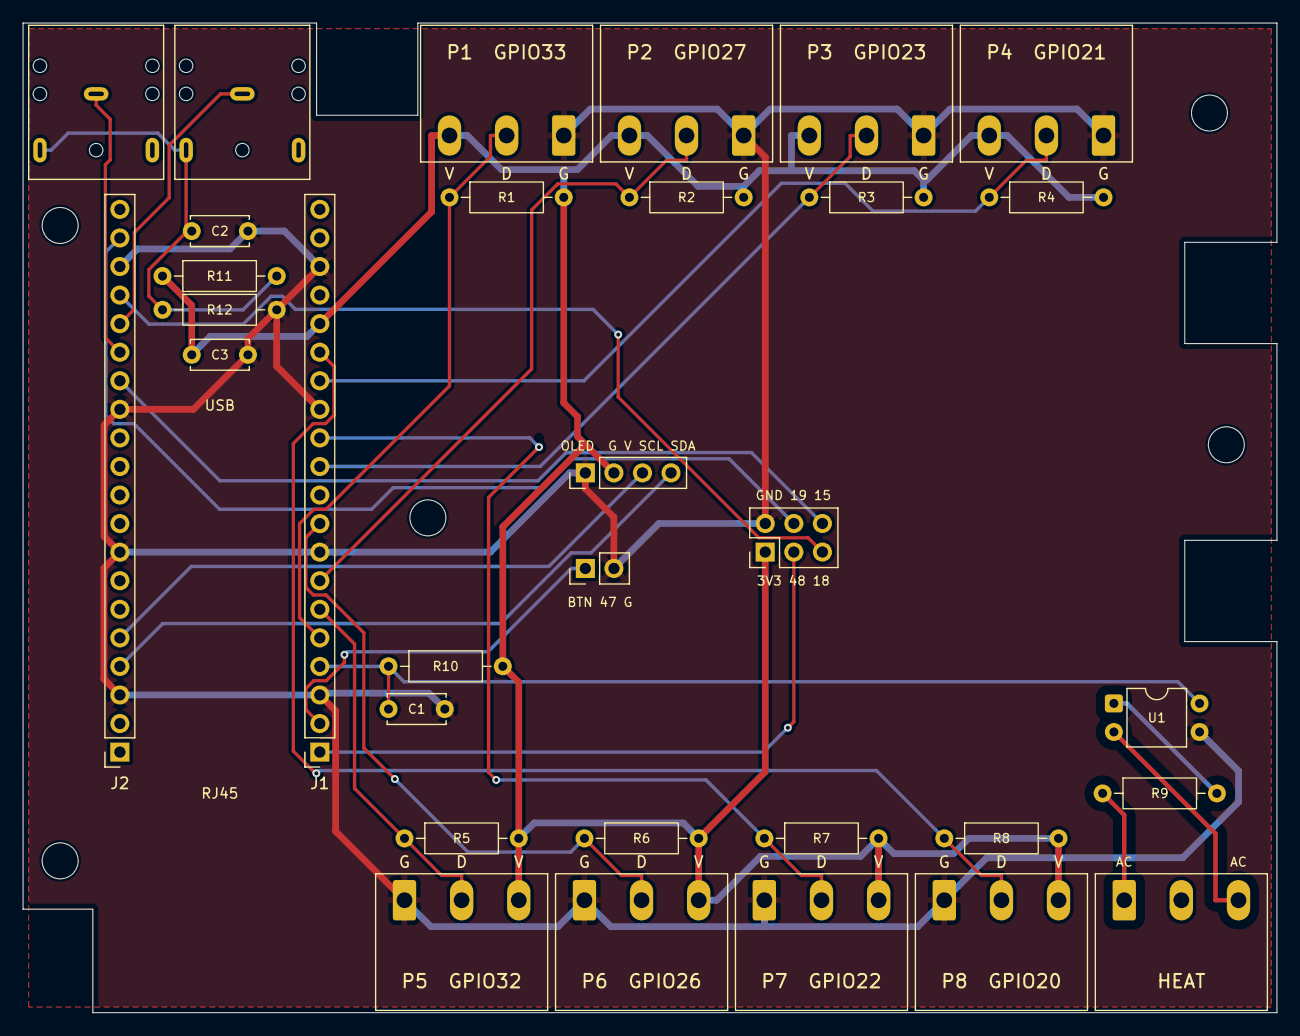
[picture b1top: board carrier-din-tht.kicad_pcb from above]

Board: 2 copper layers, 111.5 x 88.0 mm, 37 parts (0 on the bottom side), 24 nets.

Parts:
C1: 1uF; C_Disc_D5.0mm_W2.5mm_P5.00mm
C2: 10uF; C_Disc_D5.0mm_W2.5mm_P5.00mm
C3: 100nF; C_Disc_D5.0mm_W2.5mm_P5.00mm
H1, H2, H3, H4, H5: M3; MountingHole_3.2mm_M3
J1, J2: ESP32-P4-ETH; PinSocket_1x20_P2.54mm_Vertical
J3: P1; PhoenixContact_MSTBA_2,5_3-G-5,08_1x03_P5.08mm_Horizontal
J4: P2; PhoenixContact_MSTBA_2,5_3-G-5,08_1x03_P5.08mm_Horizontal
J5: P3; PhoenixContact_MSTBA_2,5_3-G-5,08_1x03_P5.08mm_Horizontal
J6: P4; PhoenixContact_MSTBA_2,5_3-G-5,08_1x03_P5.08mm_Horizontal
J7: P5; PhoenixContact_MSTBA_2,5_3-G-5,08_1x03_P5.08mm_Horizontal
J8: P6; PhoenixContact_MSTBA_2,5_3-G-5,08_1x03_P5.08mm_Horizontal
J9: P7; PhoenixContact_MSTBA_2,5_3-G-5,08_1x03_P5.08mm_Horizontal
J10: P8; PhoenixContact_MSTBA_2,5_3-G-5,08_1x03_P5.08mm_Horizontal
J11: HEAT; PhoenixContact_MSTBA_2,5_3-G-5,08_1x03_P5.08mm_Horizontal
J12: CT1; Jack_3.5mm_CUI_SJ1-3523N_Horizontal
J13: OLED; PinHeader_1x04_P2.54mm_Vertical
J14: BTN; PinHeader_1x02_P2.54mm_Vertical
J15: SPARE; PinHeader_2x03_P2.54mm_Vertical
J16: CT2; Jack_3.5mm_CUI_SJ1-3523N_Horizontal
R1, R2, R3, R4, R5, R6, R7, R8: 4.7k; R_Axial_DIN0207_L6.3mm_D2.5mm_P10.16mm_Horizontal
R9, R10, R11, R12: 10k; R_Axial_DIN0207_L6.3mm_D2.5mm_P10.16mm_Horizontal
U1: PC814; DIP-4_W7.62mm

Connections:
3V3: C3.1, J1.16, J3.3, J4.3, J5.3, J6.3, J7.3, J8.3, J9.3, J10.3, J13.2, J15.1, R1.2, R2.2, R3.2, R4.2, R5.2, R6.2, R7.2, R8.2, R10.2, R11.1
BIAS: C2.1, J12.T, J16.T, R11.2, R12.1
BTN_GPIO47: J1.2, J14.1
CT1_GPIO16: J2.15, J12.S
CT2_GPIO17: J2.16, J16.S
GND: C1.2, C2.2, C3.2, J1.3, J1.8, J1.13, J1.18, J2.3, J2.8, J2.13, J2.18, J3.1, J4.1, J5.1, J6.1, J7.1, J8.1, J9.1, J10.1, J13.1, J14.2, J15.2, R12.2, U1.3
GPIO15: J2.14, J15.6
GPIO18: J2.17, J15.5
GPIO19: J2.19, J15.4
GPIO48: J1.1, J15.3
HC_A: J11.1, R9.1
HC_B: J11.3, U1.2
HC_LED: R9.2, U1.1
HEAT_GPIO46: C1.1, J1.4, R10.1, U1.4
P1_GPIO33: J1.5, J3.2, R1.1
P2_GPIO27: J1.7, J4.2, R2.1
P3_GPIO23: J1.11, J5.2, R3.1
P4_GPIO21: J1.14, J6.2, R4.1
P5_GPIO32: J1.6, J7.2, R5.1
P6_GPIO26: J1.9, J8.2, R6.1
P7_GPIO22: J1.12, J9.2, R7.1
P8_GPIO20: J1.15, J10.2, R8.1
SCL_GPIO8: J2.5, J13.3
SDA_GPIO7: J2.4, J13.4

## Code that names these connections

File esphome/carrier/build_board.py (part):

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
import pcbnew

RESET_ROW = ["GPIO48", "GPIO47", "GND", "GPIO46", "GPIO33", "GPIO32", "GPIO27", "GND", "GPIO26", "",
             "GPIO23", "GPIO22", "GND", "GPIO21", "GPIO20", "3V3", "", "GND", "", ""]      # RUN, EN, VSYS, VBUS unused
BOOT_ROW = ["", "", "GND", "GPIO7", "GPIO8", "", "GPIO3", "GND", "GPIO4", "GPIO5",
            "GPIO6", "GPIO14", "GND", "GPIO15", "GPIO16", "GPIO17", "GPIO18", "GND", "GPIO19", "GPIO54"]

# Probe ports: name, side, centre x, GPIO. Front (RESET side) P1-P4, back (BOOT side) P5-P8, in GPIO order along
# the row so their tracks don't cross.
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             ("P4", "top", 91, "GPIO21"), ("P5", "bottom", 39, "GPIO32"), ("P6", "bottom", 55, "GPIO26"),
             ("P7", "bottom", 71, "GPIO22"), ("P8", "bottom", 87, "GPIO20")]
DIN_HEAT_X = 103.0             # HEAT block's centre, on the bottom edge
DIN_JACKS = (("J12", "CT1", 6.5, "CT1_GPIO16"), ("J16", "CT2", 19.5, "CT2_GPIO17"))    # on the top edge, centre x
DIN_HOLES = ((3.3, 18.0), (3.3, 74.5), (105.5, 8.0), (107.0, 37.5), (36.0, 44.0))      # M3, the case's standoffs
# Cut-outs in the edge for the case's pillars (the screws that join its two halves): x0, y0, x1, y1
DIN_NOTCHES = ((26.1, 0.0, 35.1, 8.2), (103.3, 19.5, DIN_W, 28.5), (103.3, 46.0, DIN_W, 55.0),
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        # pump current clamps: two 3.5 mm jacks on the top edge, beside each other, plug face flush with the edge.
        # They are 5 mm high: CT2 and the socket ends sit under the ESP board's USB end, 11 mm up.
        for ref, label, x, gpio in DIN_JACKS:
            self.jack(ref, label, x, 6.3, 180, {"S": gpio, "T": "BIAS"}, (x - 6.0, 0.2, min(x + 6.0, DIN_NOTCHES[0][0] - 0.3), 6.3 + 7.7 - 0.1))
            self.text(label, x, 16.0 if label == "CT1" else 15.6, 1.0, layer=pcbnew.B_SilkS, bold=True)
        hx = DIN_HEAT_X
        if tht:
            self.resistor("R10", "10k", 32.5, 57.2, "HEAT_GPIO46", "3V3")
            self.capacitor("C1", "1uF", 32.5, 61.0, "HEAT_GPIO46", "GND")
            self.capacitor("C2", "10uF", 15.0, 18.5, "BIAS", "GND")          # these four sit between the sockets,
            self.resistor("R11", "10k", 12.4, 22.5, "3V3", "BIAS")           # under the ESP board
            self.resistor("R12", "10k", 12.4, 25.5, "BIAS", "GND")
            self.capacitor("C3", "100nF", 15.0, 29.5, "3V3", "GND")
            self.ref_inside(self.add("Package_DIP", "DIP-4_W7.62mm", "U1", "PC814", hx - 6.0, 60.5, 0,
                                     {"1": "HC_LED", "2": "HC_B", "3": "GND", "4": "HEAT_GPIO46"}))
            self.resistor("R9", "10k", hx - 7.0, 68.5, "HC_A", "HC_LED")
        else:
            self.resistor("R10", "10k", 33.0, 57.2, "HEAT_GPIO46", "3V3", lcsc="C17414")
            self.capacitor("C1", "1uF", 37.0, 57.2, "HEAT_GPIO46", "GND", lcsc="C28323")
            self.capacitor("C2", "10uF", 16.5, 18.5, "BIAS", "GND", lcsc="C15850")
            self.resistor("R11", "10k", 14.5, 22.5, "3V3", "BIAS", lcsc="C17414")
            self.resistor("R12", "10k", 18.5, 22.5, "BIAS", "GND", lcsc="C17414")
            self.capacitor("C3", "100nF", 16.5, 29.5, "3V3", "GND", lcsc="C49678")
            self.add("Package_SO", "SO-4_4.4x3.6mm_P2.54mm", "U1", "EL814S1(A)(TU)-V", hx - 4.0, 61.5, 0,
                     {"1": "HC_LED", "2": "HC_B", "3": "GND", "4": "HEAT_GPIO46"}, lcsc="C500388")
            self.resistor("R9", "10k", hx - 5.0, 68.5, "HC_A", "HC_LED", lcsc="C17414")
        # OLED, lid button and spare GPIOs: in the open middle, where the leads have the case's full height
        self.add("Connector_PinHeader_2.54mm", "PinHeader_1x04_P2.54mm_Vertical", "J13", "OLED", 50.0, 40.0, rot=90,
                 nets={"1": "GND", "2": "3V3", "3": "SCL_GPIO8", "4": "SDA_GPIO7"}).Reference().SetVisible(False)
        self.text("OLED  G V SCL SDA", 53.8, 37.6, 0.8)
        self.add("Connector_PinHeader_2.54mm", "PinHeader_1x02_P2.54mm_Vertical", "J14", "BTN", 50.0, 48.5, rot=90,
                 nets={"1": "BTN_GPIO47", "2": "GND"}).Reference().SetVisible(False)
        self.text("BTN 47 G", 51.3, 51.5, 0.8)
        self.add("Connector_PinHeader_2.54mm", "PinHeader_2x03_P2.54mm_Vertical", "J15", "SPARE", 66.0, 47.04, rot=90,
                 nets={"1": "3V3", "2": "GND", "3": "GPIO48", "4": "GPIO19", "5": "GPIO18", "6": "GPIO15"}).Reference().SetVisible(False)
        self.text("GND 19 15", 68.5, 42.0, 0.8)
        self.text("3V3 48 18", 68.5, 49.6, 0.8)
        for ref in ("J13", "J14", "J15"):       # Dupont leads are taller than the room under the ESP board
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            for pad in fp.Pads():
                if pcbnew.ToMM(pad.GetPosition().x) < DIN_ESP_X0 + ESP_W + 2 + 1.27:
                    raise SystemExit(f"{ref} pad {pad.GetNumber()} is under (or too near) the ESP board")
        for k, n in ((3, "HEAT_GPIO46"), (1, "BTN_GPIO47"), (0, "GPIO48")):
            self.repin("J1", k, n)
        for k, n in ((14, "CT1_GPIO16"), (15, "CT2_GPIO17"), (4, "SCL_GPIO8"), (3, "SDA_GPIO7")):
            self.repin("J2", k, n)
        for name, side, cx, gpio in DIN_PORTS:
            row = "J1" if gpio in RESET_ROW else "J2"
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        # pump current clamps: two 3.5 mm jacks (CUI SJ1-3523N), plug face flush with the right edge. The SCT-013's
        # plug uses tip and sleeve only: sleeve to the ADC input, tip to BIAS (OpenEnergyMonitor's convention), ring
        # not connected.
        for ref, label, y, gpio in (("J12", "CT1", 19.0, "CT1_GPIO16"), ("J16", "CT2", 32.0, "CT2_GPIO17")):
            jk = self.add("Connector_Audio", "Jack_3.5mm_CUI_SJ1-3523N_Horizontal", ref, label, W - 6.3, y, 90,
                          {"S": gpio, "T": "BIAS"})
            jk.Reference().SetVisible(False)
            for g in list(jk.GraphicalItems()):      # the library footprint draws a board-edge cutout: not wanted here
                if g.GetLayer() == pcbnew.Edge_Cuts:
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            self.b.Add(r)
            self.text(label, 81.5, y, 1.0, bold=True)
        if tht:
            self.resistor("R10", "10k", 44.5, 25.0, "HEAT_GPIO46", "3V3")
            self.capacitor("C1", "1uF", 44.5, 28.5, "HEAT_GPIO46", "GND")
            self.capacitor("C2", "10uF", 52.5, 28.5, "BIAS", "GND")
            self.resistor("R11", "10k", 44.5, 32.0, "3V3", "BIAS")
            self.resistor("R12", "10k", 44.5, 35.5, "BIAS", "GND")
            self.ref_inside(self.add("Package_DIP", "DIP-4_W7.62mm", "U1", "PC814", 61.0, 27.0, 0,
                                     {"1": "HC_LED", "2": "HC_B", "3": "GND", "4": "HEAT_GPIO46"}))
            self.resistor("R9", "10k", 58.5, 34.5, "HC_A", "HC_LED")
            self.capacitor("C3", "100nF", 72.0, 27.0, "3V3", "GND", rot=-90)
        else:
            self.resistor("R10", "10k", 45.0, 25.5, "HEAT_GPIO46", "3V3", lcsc="C17414")
            self.capacitor("C1", "1uF", 49.0, 25.5, "HEAT_GPIO46", "GND", lcsc="C28323")
            self.capacitor("C2", "10uF", 53.0, 25.5, "BIAS", "GND", lcsc="C15850")
            self.resistor("R11", "10k", 45.0, 31.0, "3V3", "BIAS", lcsc="C17414")
            self.resistor("R12", "10k", 49.0, 31.0, "BIAS", "GND", lcsc="C17414")
            self.add("Package_SO", "SO-4_4.4x3.6mm_P2.54mm", "U1", "EL814S1(A)(TU)-V", 60.0, 28.0, 0,
                     {"1": "HC_LED", "2": "HC_B", "3": "GND", "4": "HEAT_GPIO46"}, lcsc="C500388")
            self.resistor("R9", "10k", 58.0, 34.5, "HC_A", "HC_LED", lcsc="C17414")
            self.capacitor("C3", "100nF", 72.0, 30.0, "3V3", "GND", lcsc="C49678")
        # OLED (SSD1306 module order GND VCC SCL SDA), lid button, spare GPIOs: beside the ESP board, clear of the
        # RESET/BOOT paperclip paths at x = 16.1
        self.add("Connector_PinHeader_2.54mm", "PinHeader_1x04_P2.54mm_Vertical", "J13", "OLED", 5.0, 10.5, rot=90,
                 nets={"1": "GND", "2": "3V3", "3": "SCL_GPIO8", "4": "SDA_GPIO7"}).Reference().SetVisible(False)
        self.text("OLED  G V SCL SDA", 8.8, 8.3, 0.8)
        self.add("Connector_PinHeader_2.54mm", "PinHeader_1x02_P2.54mm_Vertical", "J14", "BTN", 10.5, 53.0, rot=90,
                 nets={"1": "BTN_GPIO47", "2": "GND"}).Reference().SetVisible(False)
        self.text("BTN 47 G", 11.8, 56.0, 0.8)
        self.add("Connector_PinHeader_2.54mm", "PinHeader_2x03_P2.54mm_Vertical", "J15", "SPARE", 2.5, 48.04, rot=90,
                 nets={"1": "3V3", "2": "GND", "3": "GPIO48", "4": "GPIO19", "5": "GPIO18", "6": "GPIO15"}).Reference().SetVisible(False)
        # rotated, the header's odd pins (1 = 3V3, square) are the lower row and its even pins the upper row
        self.text("GND 19 15", 5.0, 43.0, 0.8)
        self.text("3V3 48 18", 5.0, 50.6, 0.8)
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                if ESP_Y0 - 2 - 1.27 < py < ESP_Y0 + ESP_W + 2 + 1.27:
                    raise SystemExit(f"{ref} pad {pad.GetNumber()} at y={py:.2f} is under (or too near) the ESP board")
        # socket-side nets that go to the extras
        for k, n in ((3, "HEAT_GPIO46"), (1, "BTN_GPIO47"), (0, "GPIO48")):
            self.repin("J1", k, n)
        for k, n in ((14, "CT1_GPIO16"), (15, "CT2_GPIO17"), (4, "SCL_GPIO8"), (3, "SDA_GPIO7")):
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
